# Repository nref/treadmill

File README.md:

A web service and mobile app for remote control of commercial treadmills using the GPIO pins of a Raspberry Pi. Currently, the Precor Experience 956i is supported.

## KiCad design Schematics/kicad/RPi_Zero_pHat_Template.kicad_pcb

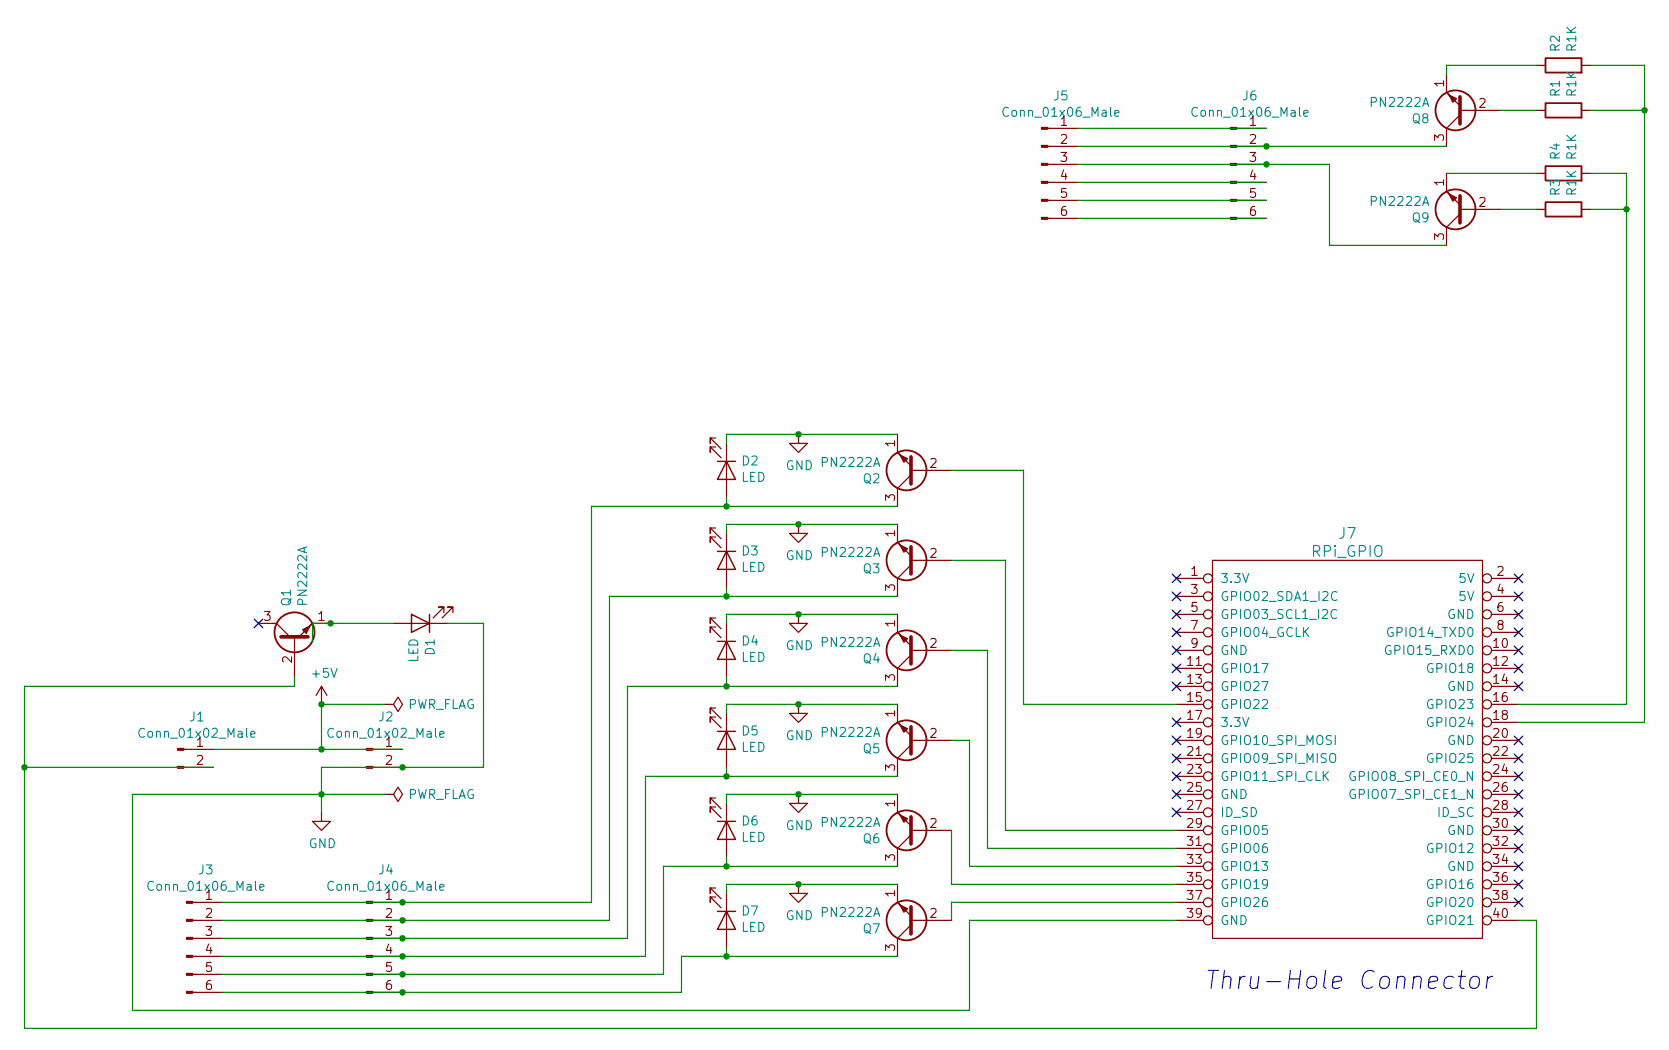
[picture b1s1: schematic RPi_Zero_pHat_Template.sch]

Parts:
D1, D2, D3, D4, D5, D6, D7: LED; LED_D3.0mm
J1, J2: Conn_01x02_Male; PinHeader_1x02_P2.54mm_Horizontal
J3, J4, J5, J6: Conn_01x06_Male; PinHeader_1x06_P2.54mm_Horizontal
J7: RPi_GPIO; Pin_Header_Straight_2x20
Q1, Q2, Q3, Q4, Q5, Q6, Q7, Q8, Q9: PN2222A; TO-92_Inline
R1, R2, R3, R4: R1K; R_Axial_DIN0204_L3.6mm_D1.6mm_P7.62mm_Horizontal

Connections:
+5V: J1.1, J2.1
GND: D1.1 (K), D2.1 (K), D3.1 (K), D4.1 (K), D5.1 (K), D6.1 (K), D7.1 (K), J2.2, J7.39 (GND), Q2.1 (E), Q3.1 (E), Q4.1 (E), Q5.1 (E), Q6.1 (E), Q7.1 (E)
unnamed: D1.2 (A), Q1.1 (E)
unnamed: D2.2 (A), J3.1, J4.1, Q2.3 (C)
unnamed: D3.2 (A), J3.2, J4.2, Q3.3 (C)
unnamed: D4.2 (A), J3.3, J4.3, Q4.3 (C)
unnamed: D5.2 (A), J3.4, J4.4, Q5.3 (C)
unnamed: D6.2 (A), J3.5, J4.5, Q6.3 (C)
unnamed: D7.2 (A), J3.6, J4.6, Q7.3 (C)
unnamed: J1.2, J7.40 (GPIO21), Q1.2 (B)
unnamed: J5.1, J6.1
unnamed: J5.2, J6.2, Q8.3 (C)
unnamed: J5.3, J6.3, Q9.3 (C)
unnamed: J5.4, J6.4
unnamed: J5.5, J6.5
unnamed: J5.6, J6.6
unnamed: J7.15 (GPIO22), Q2.2 (B)
unnamed: J7.16 (GPIO23), R3.2, R4.2
unnamed: J7.18 (GPIO24), R1.2, R2.2
unnamed: J7.29 (GPIO05), Q3.2 (B)
unnamed: J7.31 (GPIO06), Q4.2 (B)
unnamed: J7.33 (GPIO13), Q5.2 (B)
unnamed: J7.35 (GPIO19), Q6.2 (B)
unnamed: J7.37 (GPIO26), Q7.2 (B)
unnamed: Q8.1 (E), R2.1
unnamed: Q8.2 (B), R1.1
unnamed: Q9.1 (E), R4.1
unnamed: Q9.2 (B), R3.1

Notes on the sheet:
Thru-Hole Connector

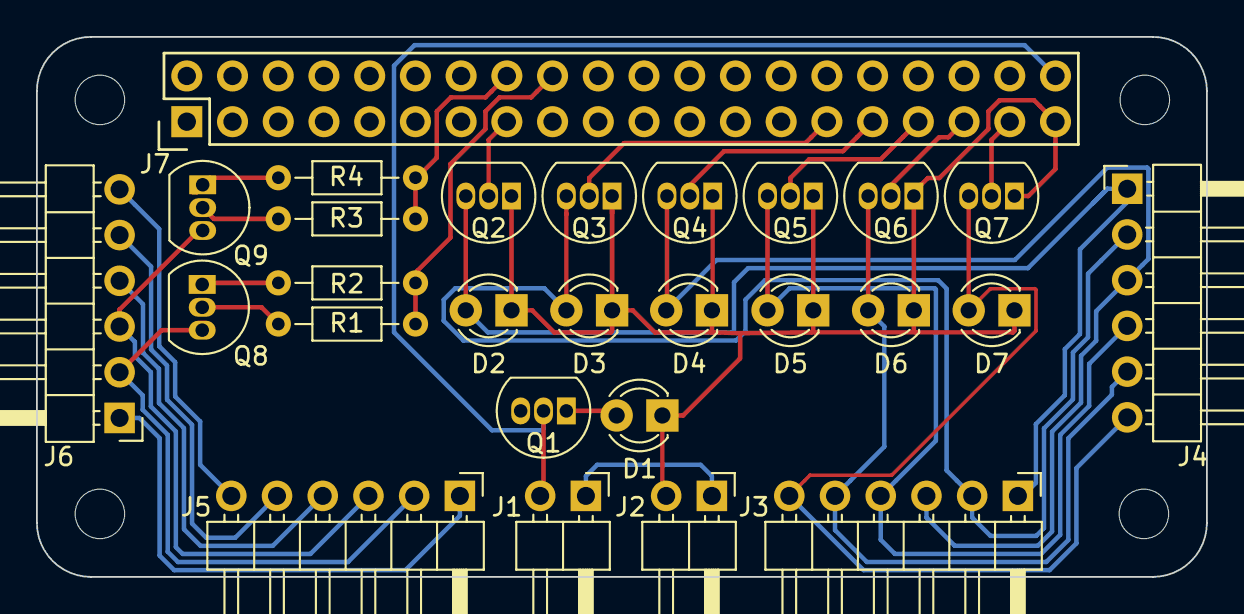
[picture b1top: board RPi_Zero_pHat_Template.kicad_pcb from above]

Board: 2 copper layers, 65.0 x 30.0 mm, 28 parts (0 on the bottom side), 28 nets.

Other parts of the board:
ee: RPi_Hat_Mounting_Hole

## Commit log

2020-02-14 Add android client. Move webservice into its own directory
2020-02-14 Fix i2c include broken after directory reorg. Chain i2c makefile from webservice makefile
2020-02-14 Fix grammar
2020-02-14 Rename webservice to service
2020-02-14 Rename service to services
2020-02-14 Add socket communication between i2c and server
2020-02-14 Promote socket to class scope
2020-02-15 Add http callbacks
2020-02-16 Work on http callbacks
2020-02-16 Handle callbacks in the Android client. Extract MainViewModel, MainView
2020-02-18 Add udp health check in client
2020-02-18 Add udp metric callback and health check
2020-02-18 Use Caliburn.Micro and Ninject
2020-02-18 Extract DomainServices out of MainViewModel
2020-02-28 Split up into multiple views
2020-02-28 i2c send full message one instead of char-by-char. webservice detect when treadmill stop and start buttons are pressed externally
2020-06-12 Lots of front-end work
2020-08-11 WorkoutSegment add ability specify incline
2020-08-11 Temporary changes to use LED activation count instead of i2c feedback as metrics feedback. Add service installer
2020-08-11 gitignore log files
2020-08-11 Namespace reflactoring
2020-08-13 Add a self-hosted web API
2020-08-13 Switch DI from Lamar to Ninject which works on Android
2020-08-13 Fix namespace typo Treadmil.Infrastructure'
2020-08-15 Major refactoring. Add ServiceHost. Break up TreadmillService, rename it to RemoteTreadmillAdapter.
2020-08-15 Rename IloggingService to ILogService. Inject it in a few new places. WorkoutView show Distance and Percent complete
2020-08-17 Update package dependencies. WIP workout editor
2020-08-22 Restore use of actual metrics
2020-08-22 WIP Android UI rework
2020-08-22 installer install dependencies
2020-11-30 WIP small device support. Add confirm dialogs for add/remove workout, add/remove workout segment. Add some hardcoded workouts
2020-12-09 update service file
2020-12-09 Add more workouts
2020-12-09 Disable buggy state validation
2020-12-12 Add kicad schematics.
    At the moment the GPIO pins in the schematic do not match the pins used
    in the service (precor956i.py) because after sending the schematic to OSHPark for
    printing, the board did not work as expected on some GPIO pins. Suspecting
    some of my Raspberry Pi ZeroW pins were defective, I changed the pins. I
    suspected the pins were bad because I had briefly exposed them to 5v,
    and they are rated 3.3v. I also bought a new Raspberry Pi Zerow.
2020-12-12 Remove kicad
2020-12-12 Add schematics again.
    They were not added last time because the kicad folder contained a .git
    folder, which I deleted after adding, but did not git add again.
2020-12-14 Clean up csproj files
2020-12-14 Replace use of System.Text.Json with Newtonsoft.Json.
    We were using Newtonsoft in one place and System.Text.Json in the other.
    Use just one.
2020-12-19 Add screenshot to README
2022-02-01 Update icons
2022-02-01 Add toast notification service
2022-02-01 Add editorconfig
2022-02-01 Add next and previous buttons; show pace instead of speed; show segment time remaining instead of % complete; show toast notification when setting speed/incline.
2022-02-01 Add C25K workouts
2022-03-14 Add upca.sln
2022-06-09 Migrate from Xamarin.Forms to MAUI
2022-06-10 Use Shell DI
2022-06-23 Bump Newtonsoft.Json from 12.0.3 to 13.0.1 in /Application/Treadmill.Ui
    Bumps [Newtonsoft.Json](https://github.com/JamesNK/Newtonsoft.Json) from 12.0.3 to 13.0.1.
    - [Release notes](https://github.com/JamesNK/Newtonsoft.Json/releases)
    - [Commits](https://github.com/JamesNK/Newtonsoft.Json/compare/12.0.3...13.0.1)
    ---
    updated-dependencies:
    - dependency-name: Newtonsoft.Json
2022-06-23 Bump Newtonsoft.Json
    Bumps [Newtonsoft.Json](https://github.com/JamesNK/Newtonsoft.Json) from 12.0.3 to 13.0.1.
    - [Release notes](https://github.com/JamesNK/Newtonsoft.Json/releases)
    - [Commits](https://github.com/JamesNK/Newtonsoft.Json/compare/12.0.3...13.0.1)
    ---
    updated-dependencies:
    - dependency-name: Newtonsoft.Json
2022-06-23 Bump Newtonsoft.Json in /Infrastructure/Treadmill.Adapters.Gpio
    Bumps [Newtonsoft.Json](https://github.com/JamesNK/Newtonsoft.Json) from 12.0.3 to 13.0.1.
    - [Release notes](https://github.com/JamesNK/Newtonsoft.Json/releases)
    - [Commits](https://github.com/JamesNK/Newtonsoft.Json/compare/12.0.3...13.0.1)
    ---
    updated-dependencies:
    - dependency-name: Newtonsoft.Json
2022-06-29 End workout if no contact from treadmill
2022-06-29 Create log before tail
2022-06-30 Update timestamp for all messages not just changes
2022-06-30 Send treadmill state to clients
2022-06-30 Add TreadmillMetric.State
2022-06-30 Make treadmill state a metric; android app subscribe to state changes
2022-06-30 Fix syntax errors; set state sooner
2022-06-30 Don't poll; bump newtonsoft json
2022-06-30 Reach setpoints fast: hold pin for large diffs
2022-06-30 Prefer specific local IPs
2022-07-01 Add comment
2022-07-10 Send a message to lcpa
